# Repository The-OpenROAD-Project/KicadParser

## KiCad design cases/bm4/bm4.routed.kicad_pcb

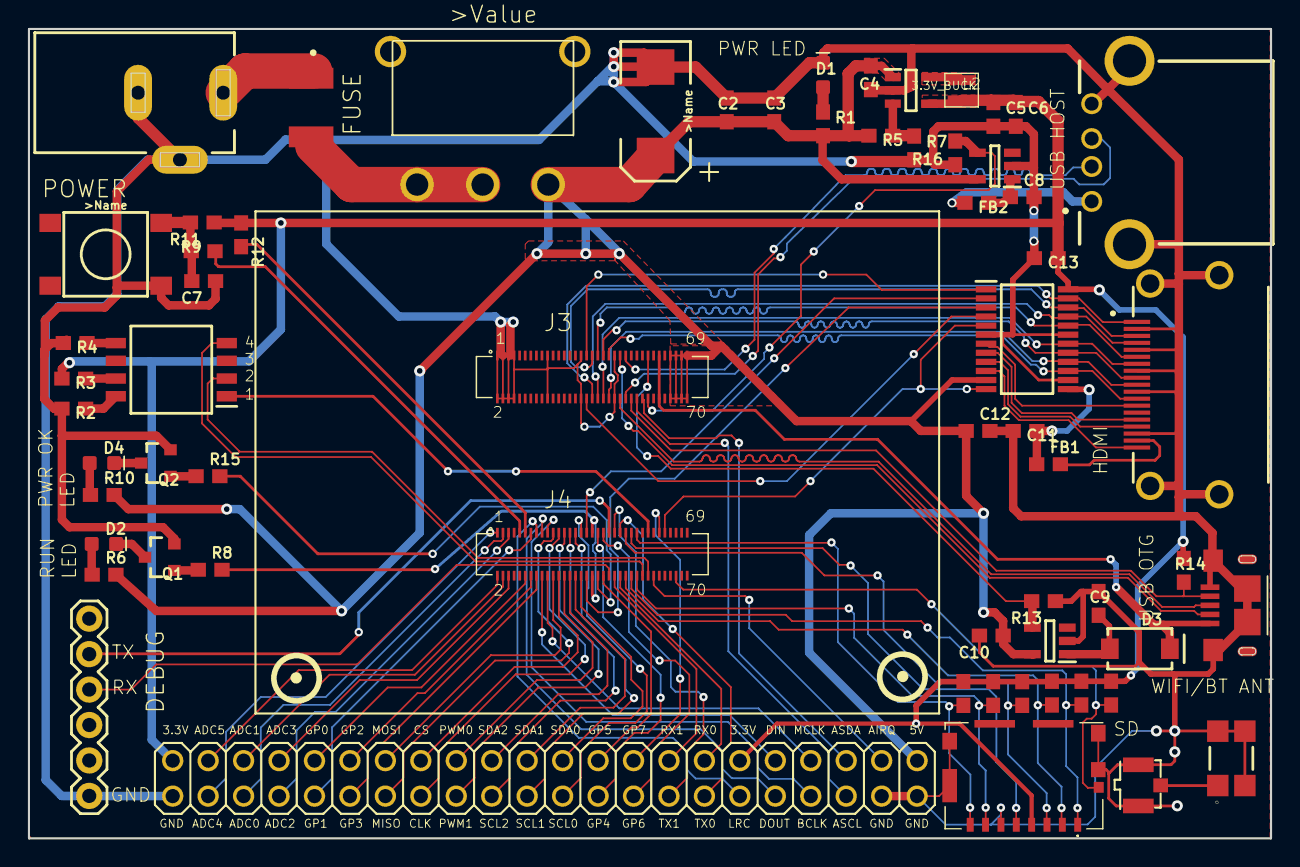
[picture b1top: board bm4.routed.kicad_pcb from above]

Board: 2 copper layers, 89.0 x 58.0 mm, 63 parts (0 on the bottom side), 103 nets.

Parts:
3.3V_BUCK: LM3671MF-3.3_NOPB; SOT95P284X122-5N
ANT1: 146175-0001
C1: 100uF; EIA7343
C2, C5, C10: 10uF; 0603
C3, C6, C11, C12, C13: 0.1uF; 0603
C4, C8, C9: 4.7uF; 0603
C7: 1.0uF; 0603
D1: Red; LED-0603
D2: GREEN; LED-0603
D3: 3A/40V/500mV; SMA-DIODE
D4: BLUE; LED-0603
F1: MF-MSMF260-2
FB1: 120Ω; 0603
FB2: 30Ω; 0603
IC2, IC4: TPS2051BDBVR; SOT95P280X145-5N
IC3: TPD12S016PWR; SOP65P640X120-24N
J1: DCJ0202
J2: 10118193-0001LF
J3, J4: DF40C(2.0)-70DS-0.4V(51)
J5: UE27AC54100
J6: 6_PIN_SERIAL_CABLEPTH; FTDI_BASIC
J7: 10029449-111RLF; 10029449-111RLF_1
J8: 1051620001
L2: NRH2412T2R2MNGH
Q1, Q2: 600mA/40V; SOT23-3
R1, R6, R10: 470; 0603
R2, R3, R4: 1k; 0603
R5, R8, R13, R15, R17, R20: 10k; 0603
R7, R11, R12, R14, R16: 100k; 0603
R9: 33; 0603
R18, R19, R21, R22: 51k; 0603
S1: MOMENTARY-SWITCH-SPST-SMD-6.2MM-TALL; TACTILE_SWITCH_SMD_6.2MM_TALL
S3: 218-4LPST; SOIC127P844X265-8N
SV1: TEST HEADER; 2X22
SW1: 500SSP1S1M6QEA
U$3: U.FL-R-SMT(10)

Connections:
3.3V: 3.3V_BUCK.4, C5.1, C6.1, C13.1, IC3.24, J8.4, L2.2, R3.2, R11.1, R12.1, R14.2, R17.2, R18.2, R19.2, R20.2, R21.2, R22.2, SV1.2, SV1.34
5V: 3.3V_BUCK.1, C1.A, C2.1, C3.1, C4.1, C10.1, C12.1, IC2.5, IC3.11, IC4.5, J3.63, J3.64, J3.65, J3.66, J3.67, J3.68, J3.69, J3.70, R1.2, R5.2, R6.2, R10.2, SV1.44, SW1.3
GND: 3.3V_BUCK.2, ANT1.2, ANT1.3, ANT1.4, C1.C, C2.2, C3.2, C4.2, C5.2, C6.2, C7.1, C8.2, C9.2, C10.2, C11.2, C12.2, C13.2, D1.C, IC2.2, IC3.6, IC3.14, IC3.19, IC4.2, J1.2, J1.3, J2.GND, J2.SHIELD$1, J2.SHIELD$2, J2.SHIELD$3, J2.SHIELD$4, J3.1, J3.2, J3.3, J3.4, J3.5, J3.6, J3.7, J3.8, J3.19, J3.20, J3.31, J3.32, J3.43, J3.44, J5.4, J5.5, J5.6, J6.GND, J7.2, J7.5, J7.8, J7.11, J7.17, J7.20, J7.21, J7.22, J7.23, J8.6, J8.10, J8.11, J8.12, J8.13, Q1.2, Q2.2, R2.2, R4.2, R7.2, R13.1, R16.1, S1.A2, SV1.1, SV1.41, SV1.43, U$3.1, U$3.2
unnamed: F1.1, J1.1
unnamed: F1.2, SW1.1, SW1.2
unnamed: 3.3V_BUCK.5, L2.1
unnamed: D1.A, R1.1
unnamed: R2.1, S3.8
unnamed: R3.1, S3.7
unnamed: R4.1, S3.5
unnamed: D2.A, R6.1
unnamed: 3.3V_BUCK.3, R5.1, R7.1
unnamed: D2.C, Q1.3
unnamed: Q1.1, R8.1
unnamed: C7.2, R9.1, R11.2, S1.B2
unnamed: D4.A, R10.1
unnamed: C11.1, FB1.1, IC3.13
unnamed: C9.1, D3.A, IC2.1
unnamed: IC3.7, J7.13
unnamed: IC3.8, J7.15
unnamed: IC3.9, J7.16
unnamed: IC3.10, J7.19
unnamed: D4.C, Q2.3
unnamed: Q2.1, R15.1
unnamed: FB1.2, J7.18
unnamed: C8.1, FB2.1, IC4.1
unnamed: FB2.2, J5.1
unnamed: ANT1.1, U$3.3
VCC5P0_OTG: D3.C, J2.VCC, J3.59, J3.60
VSYS_IO_3P3: J4.35, J4.36, R8.2
XADC0: J4.3, SV1.5
XADC1: J4.4, SV1.6
XADC2: J4.5, SV1.7
XADC3: J4.6, SV1.8
XADC4: J4.1, SV1.3
XADC5: J4.2, SV1.4
XAUDIO_IRQ: J4.58, SV1.42
XAUDIO_SCL: J3.52, SV1.39
XAUDIO_SDA: J3.54, SV1.40
XBOOT_CONFIG0: J4.55, S3.1
XBOOT_CONFIG1: J4.56, S3.2
XBOOT_CONFIG3: J4.54, S3.4
XDEBUG_RX: J4.42, J6.TXO
XDEBUG_TX: J4.41, J6.RXI
XGPA15: IC2.4, J3.55, R13.2
XGPA16: IC4.4, J3.56, R16.2
XGPA21: IC3.5, IC3.12, J4.61
XGPIO0: J4.12, SV1.10
XGPIO1: J4.13, SV1.9
XGPIO2: J4.14, SV1.12
XGPIO3: J4.16, SV1.11
XGPIO4: J4.37, SV1.25
XGPIO5: J4.40, SV1.26
XGPIO6: J4.39, SV1.27
XGPIO7: J4.59, SV1.28
XHDMI_CEC: IC3.1, J3.33
XHDMI_HPD: IC3.4, J3.34
XHDMI_I2C_SCL: IC3.2, J4.33
XHDMI_I2C_SDA: IC3.3, J4.34
XHDMI_TX0_N: IC3.17, J3.39, J7.9
XHDMI_TX0_P: IC3.18, J3.40, J7.7
XHDMI_TX1_N: IC3.20, J3.37, J7.6
XHDMI_TX1_P: IC3.21, J3.38, J7.4
XHDMI_TX2_N: IC3.22, J3.35, J7.3
XHDMI_TX2_P: IC3.23, J3.36, J7.1
XHDMI_TXC_N: IC3.15, J3.41, J7.12
XHDMI_TXC_P: IC3.16, J3.42, J7.10
XI2C_SCL0: J4.31, SV1.23
XI2C_SCL1: J4.29, SV1.21
XI2C_SCL2: J4.27, SV1.19
XI2C_SDA0: J4.32, SV1.24
XI2C_SDA1: J4.30, SV1.22
XI2C_SDA2: J4.28, SV1.20
XI2S0_BCLK: J4.19, SV1.37
XI2S0_DIN: J4.18, SV1.36
XI2S0_DOUT: J4.17, SV1.35
XI2S0_LRCLK: J4.15, SV1.33
XI2S0_MCLK: J4.20, SV1.38
XNRESET: J4.11, R12.2
XOTG_D_N: J2.D-, J3.45
XOTG_D_P: J2.D+, J3.46
XOTG_ID: J2.ID, J3.50, R14.1
XPWERKEY: J4.9, R9.2
XPWM0: J4.26, SV1.18
XPWM1: J4.25, SV1.17
XSD0_CDN: J4.66, J8.9, R17.1
XSD0_CLK: J4.49, J8.5
XSD0_CMD: J4.47, J8.3, R19.1
XSD0_D0: J4.52, J8.7, R20.1
XSD0_D1: J4.51, J8.8, R18.1
XSD0_D2: J4.50, J8.1, R21.1
XSD0_D3: J4.48, J8.2, R22.1
XSPI_CLK: J4.23, SV1.15
XSPI_CS: J4.24, SV1.16
XSPI_MISO: J4.21, SV1.13
XSPI_MOSI: J4.22, SV1.14
XUART_RX0: J4.46, SV1.32
XUART_RX1: J4.44, SV1.30
XUART_TX0: J4.45, SV1.31
XUART_TX1: J4.43, SV1.29
XUSBH_D_N: J3.47, J5.2
XUSBH_D_P: J3.48, J5.3
XVDDPWRON: J4.38, R15.2

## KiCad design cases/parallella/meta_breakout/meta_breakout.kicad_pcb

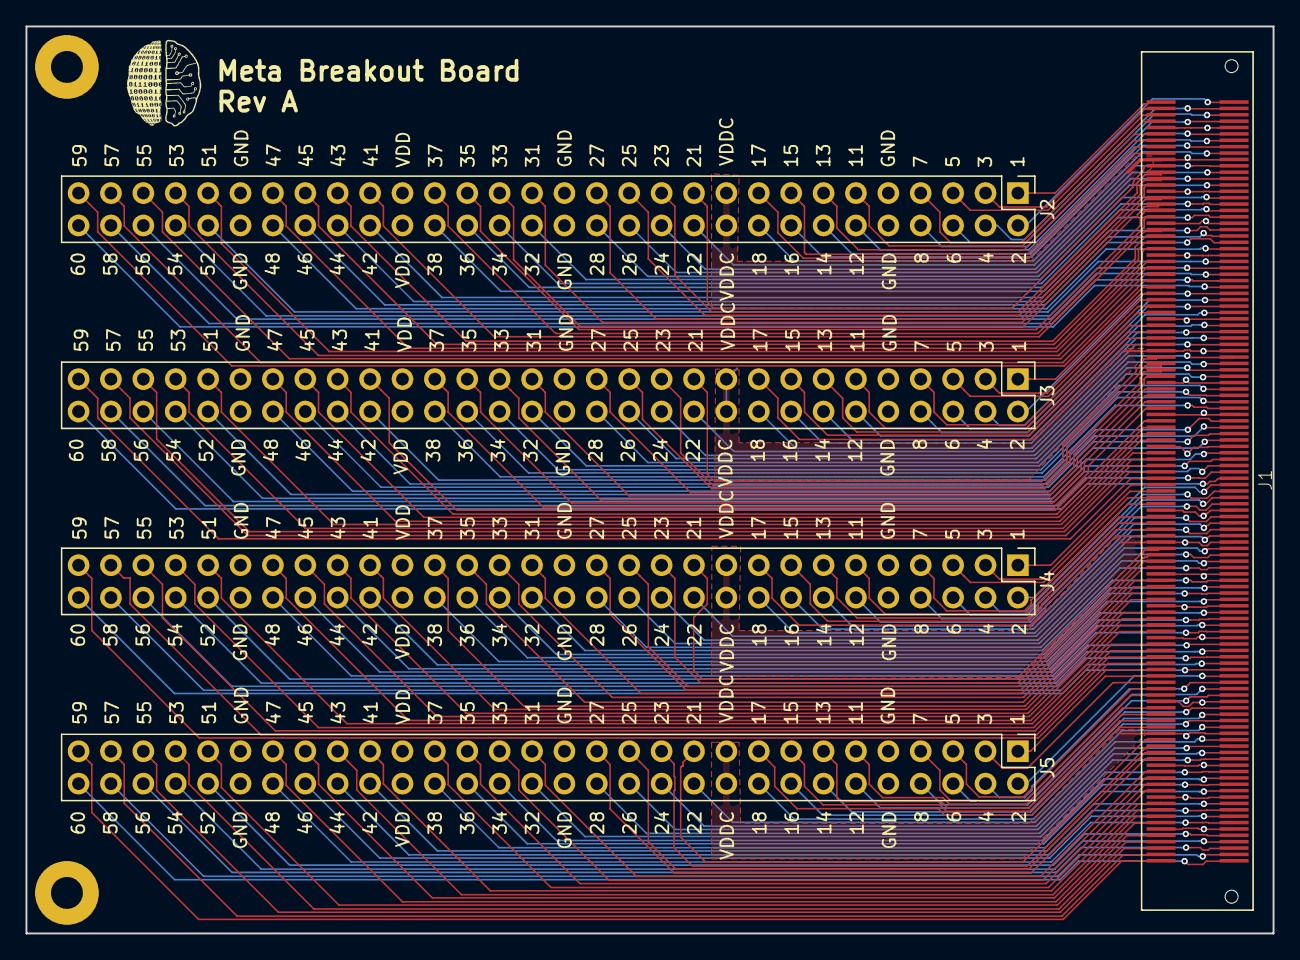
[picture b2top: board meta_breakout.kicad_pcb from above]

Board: 4 copper layers, 97.8 x 71.1 mm, 5 parts (0 on the bottom side), 209 nets.

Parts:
J1: BSH-120; BSH-120-01-X-D-A
J2, J3, J4, J5: Conn_02x30_Odd_Even; PinHeader_2x30_P2.54mm_Vertical

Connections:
/CTRL_IN0: J1.59, J2.59
/CTRL_IN1: J1.119, J3.59
/CTRL_IN2: J1.179, J4.59
/CTRL_IN3: J1.239, J5.59
/CTRL_OUT0: J1.60, J2.60
/CTRL_OUT1: J1.120, J3.60
/CTRL_OUT2: J1.180, J4.60
/CTRL_OUT3: J1.240, J5.60
/DATA_IN_N0: J1.21, J2.21
/DATA_IN_N1: J1.25, J2.25
/DATA_IN_N2: J1.31, J2.31
/DATA_IN_N3: J1.35, J2.35
/DATA_IN_N4: J1.41, J2.41
/DATA_IN_N5: J1.45, J2.45
/DATA_IN_N6: J1.51, J2.51
/DATA_IN_N7: J1.55, J2.55
/DATA_IN_N8: J1.81, J3.21
/DATA_IN_N9: J1.85, J3.25
/DATA_IN_N10: J1.91, J3.31
/DATA_IN_N11: J1.95, J3.35
/DATA_IN_N12: J1.101, J3.41
/DATA_IN_N13: J1.105, J3.45
/DATA_IN_N14: J1.111, J3.51
/DATA_IN_N15: J1.115, J3.55
/DATA_IN_N16: J1.141, J4.21
/DATA_IN_N17: J1.145, J4.25
/DATA_IN_N18: J1.151, J4.31
/DATA_IN_N19: J1.155, J4.35
/DATA_IN_N20: J1.161, J4.41
/DATA_IN_N21: J1.165, J4.45
/DATA_IN_N22: J1.171, J4.51
/DATA_IN_N23: J1.175, J4.55
/DATA_IN_N24: J1.201, J5.21
/DATA_IN_N25: J1.205, J5.25
/DATA_IN_N26: J1.211, J5.31
/DATA_IN_N27: J1.215, J5.35
/DATA_IN_N28: J1.221, J5.41
/DATA_IN_N29: J1.225, J5.45
/DATA_IN_N30: J1.231, J5.51
/DATA_IN_N31: J1.235, J5.55
/DATA_IN_P0: J1.23, J2.23
/DATA_IN_P1: J1.27, J2.27
/DATA_IN_P2: J1.33, J2.33
/DATA_IN_P3: J1.37, J2.37
/DATA_IN_P4: J1.43, J2.43
/DATA_IN_P5: J1.47, J2.47
/DATA_IN_P6: J1.53, J2.53
/DATA_IN_P7: J1.57, J2.57
/DATA_IN_P8: J1.83, J3.23
/DATA_IN_P9: J1.87, J3.27
/DATA_IN_P10: J1.93, J3.33
/DATA_IN_P11: J1.97, J3.37
/DATA_IN_P12: J1.103, J3.43
/DATA_IN_P13: J1.107, J3.47
/DATA_IN_P14: J1.113, J3.53
/DATA_IN_P15: J1.117, J3.57
/DATA_IN_P16: J1.143, J4.23
/DATA_IN_P17: J1.147, J4.27
/DATA_IN_P18: J1.153, J4.33
/DATA_IN_P19: J1.157, J4.37
/DATA_IN_P20: J1.163, J4.43
/DATA_IN_P21: J1.167, J4.47
/DATA_IN_P22: J1.173, J4.53
/DATA_IN_P23: J1.177, J4.57
/DATA_IN_P24: J1.203, J5.23
/DATA_IN_P25: J1.207, J5.27
/DATA_IN_P26: J1.213, J5.33
/DATA_IN_P27: J1.217, J5.37
/DATA_IN_P28: J1.223, J5.43
/DATA_IN_P29: J1.227, J5.47
/DATA_IN_P30: J1.233, J5.53
/DATA_IN_P31: J1.237, J5.57
/DATA_OUT_N0: J1.22, J2.22
/DATA_OUT_N1: J1.26, J2.26
/DATA_OUT_N2: J1.32, J2.32
/DATA_OUT_N3: J1.36, J2.36
/DATA_OUT_N4: J1.42, J2.42
/DATA_OUT_N5: J1.46, J2.46
/DATA_OUT_N6: J1.52, J2.52
/DATA_OUT_N7: J1.56, J2.56
/DATA_OUT_N8: J1.82, J3.22
/DATA_OUT_N9: J1.86, J3.26
/DATA_OUT_N10: J1.92, J3.32
/DATA_OUT_N11: J1.96, J3.36
/DATA_OUT_N12: J1.102, J3.42
/DATA_OUT_N13: J1.106, J3.46
/DATA_OUT_N14: J1.112, J3.52
/DATA_OUT_N15: J1.116, J3.56
/DATA_OUT_N16: J1.142, J4.22
/DATA_OUT_N17: J1.146, J4.26
/DATA_OUT_N18: J1.152, J4.32
/DATA_OUT_N19: J1.156, J4.36
/DATA_OUT_N20: J1.162, J4.42
/DATA_OUT_N21: J1.166, J4.46
/DATA_OUT_N22: J1.172, J4.52
/DATA_OUT_N23: J1.176, J4.56
/DATA_OUT_N24: J1.202, J5.22
/DATA_OUT_N25: J1.206, J5.26
/DATA_OUT_N26: J1.212, J5.32
/DATA_OUT_N27: J1.216, J5.36
/DATA_OUT_N28: J1.222, J5.42
/DATA_OUT_N29: J1.226, J5.46
/DATA_OUT_N30: J1.232, J5.52
/DATA_OUT_N31: J1.236, J5.56
/DATA_OUT_P0: J1.24, J2.24
/DATA_OUT_P1: J1.28, J2.28
/DATA_OUT_P2: J1.34, J2.34
/DATA_OUT_P3: J1.38, J2.38
/DATA_OUT_P4: J1.44, J2.44
/DATA_OUT_P5: J1.48, J2.48
/DATA_OUT_P6: J1.54, J2.54
/DATA_OUT_P7: J1.58, J2.58
/DATA_OUT_P8: J1.84, J3.24
/DATA_OUT_P9: J1.88, J3.28
/DATA_OUT_P10: J1.94, J3.34
/DATA_OUT_P11: J1.98, J3.38
/DATA_OUT_P12: J1.104, J3.44
/DATA_OUT_P13: J1.108, J3.48
/DATA_OUT_P14: J1.114, J3.54
/DATA_OUT_P15: J1.118, J3.58
/DATA_OUT_P16: J1.144, J4.24
/DATA_OUT_P17: J1.148, J4.28
/DATA_OUT_P18: J1.154, J4.34
/DATA_OUT_P19: J1.158, J4.38
/DATA_OUT_P20: J1.164, J4.44
/DATA_OUT_P21: J1.168, J4.48
/DATA_OUT_P22: J1.174, J4.54
/DATA_OUT_P23: J1.178, J4.58
/DATA_OUT_P24: J1.204, J5.24
/DATA_OUT_P25: J1.208, J5.28
/DATA_OUT_P26: J1.214, J5.34
/DATA_OUT_P27: J1.218, J5.38
/DATA_OUT_P28: J1.224, J5.44
/DATA_OUT_P29: J1.228, J5.48
/DATA_OUT_P30: J1.234, J5.54
/DATA_OUT_P31: J1.238, J5.58
/FRAME_IN_N0: J1.5, J2.5
/FRAME_IN_N1: J1.65, J3.5
/FRAME_IN_N2: J1.125, J4.5
/FRAME_IN_N3: J1.185, J5.5
/FRAME_IN_P0: J1.7, J2.7
/FRAME_IN_P1: J1.67, J3.7
/FRAME_IN_P2: J1.127, J4.7
/FRAME_IN_P3: J1.187, J5.7
/FRAME_OUT_N0: J1.6, J2.6
/FRAME_OUT_N1: J1.66, J3.6
/FRAME_OUT_N2: J1.126, J4.6
/FRAME_OUT_N3: J1.186, J5.6
/FRAME_OUT_P0: J1.8, J2.8
/FRAME_OUT_P1: J1.68, J3.8
/FRAME_OUT_P2: J1.128, J4.8
/FRAME_OUT_P3: J1.188, J5.8
/GND: J1.9, J1.10, J1.29, J1.30, J1.49, J1.50, J1.69, J1.70, J1.89, J1.90, J1.109, J1.110, J1.129, J1.130, J1.149, J1.150, J1.169, J1.170, J1.189, J1.190, J1.209, J1.210, J1.229, J1.230, J2.9, J2.10, J2.29, J2.30, J2.49, J2.50, J3.9, J3.10, J3.29, J3.30, J3.49, J3.50, J4.9, J4.10, J4.29, J4.30, J4.49, J4.50, J5.9, J5.10, J5.29, J5.30, J5.49, J5.50
/LCLK_IN_N0: J1.1, J2.1
/LCLK_IN_N1: J1.61, J3.1
/LCLK_IN_N2: J1.121, J4.1
/LCLK_IN_N3: J1.181, J5.1
/LCLK_IN_P0: J1.3, J2.3
/LCLK_IN_P1: J1.63, J3.3
/LCLK_IN_P2: J1.123, J4.3
/LCLK_IN_P3: J1.183, J5.3
/LCLK_OUT_N0: J1.2, J2.2
/LCLK_OUT_N1: J1.62, J3.2
/LCLK_OUT_N2: J1.122, J4.2
/LCLK_OUT_N3: J1.182, J5.2
/LCLK_OUT_P0: J1.4, J2.4
/LCLK_OUT_P1: J1.64, J3.4
/LCLK_OUT_P2: J1.124, J4.4
/LCLK_OUT_P3: J1.184, J5.4
/VDD0: J1.19, J1.20, J2.19, J2.20
/VDD1: J1.79, J1.80, J3.19, J3.20
/VDD2: J1.139, J1.140, J4.19, J4.20
/VDD3: J1.199, J1.200, J5.19, J5.20
/VDDIO0: J1.39, J1.40, J2.39, J2.40
/VDDIO1: J1.99, J1.100, J3.39, J3.40
/VDDIO2: J1.159, J1.160, J4.39, J4.40
/VDDIO3: J1.219, J1.220, J5.39, J5.40
/WAIT_RD_IN_N0: J1.16, J2.16
/WAIT_RD_IN_N1: J1.76, J3.16
/WAIT_RD_IN_N2: J1.136, J4.16
/WAIT_RD_IN_N3: J1.196, J5.16
/WAIT_RD_IN_P0: J1.18, J2.18
/WAIT_RD_IN_P1: J1.78, J3.18
/WAIT_RD_IN_P2: J1.138, J4.18
/WAIT_RD_IN_P3: J1.198, J5.18
/WAIT_RD_OUT_N0: J1.15, J2.15
/WAIT_RD_OUT_N1: J1.75, J3.15
/WAIT_RD_OUT_N2: J1.135, J4.15
/WAIT_RD_OUT_N3: J1.195, J5.15
/WAIT_RD_OUT_P0: J1.17, J2.17
/WAIT_RD_OUT_P1: J1.77, J3.17
/WAIT_RD_OUT_P2: J1.137, J4.17
/WAIT_RD_OUT_P3: J1.197, J5.17
/WAIT_WR_IN_N0: J1.12, J2.12
/WAIT_WR_IN_N1: J1.72, J3.12
/WAIT_WR_IN_N2: J1.132, J4.12
/WAIT_WR_IN_N3: J1.192, J5.12
/WAIT_WR_IN_P0: J1.14, J2.14
/WAIT_WR_IN_P1: J1.74, J3.14
/WAIT_WR_IN_P2: J1.134, J4.14
/WAIT_WR_IN_P3: J1.194, J5.14
/WAIT_WR_OUT_N0: J1.11, J2.11
/WAIT_WR_OUT_N1: J1.71, J3.11
/WAIT_WR_OUT_N2: J1.131, J4.11
/WAIT_WR_OUT_N3: J1.191, J5.11
/WAIT_WR_OUT_P0: J1.13, J2.13
/WAIT_WR_OUT_P1: J1.73, J3.13
/WAIT_WR_OUT_P2: J1.133, J4.13
/WAIT_WR_OUT_P3: J1.193, J5.13

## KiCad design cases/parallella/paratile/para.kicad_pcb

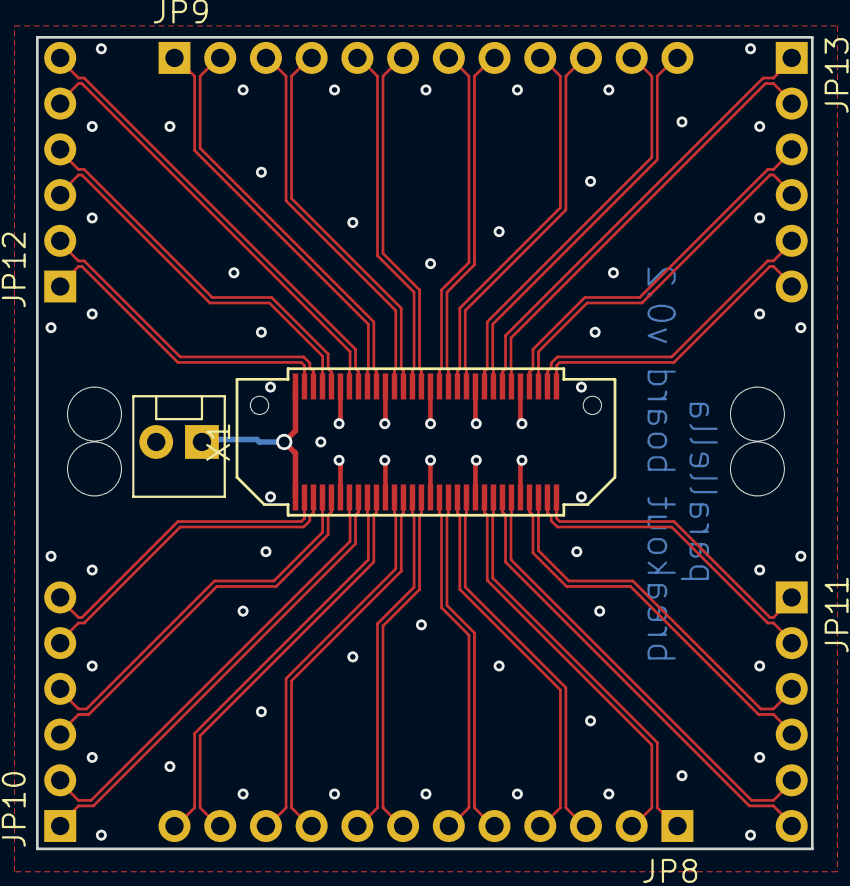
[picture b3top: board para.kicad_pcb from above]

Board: 2 copper layers, 43.1 x 45.1 mm, 13 parts (0 on the bottom side), 50 nets.

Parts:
@HOLE0, @HOLE1, @HOLE2, @HOLE3: (no value)
C2: CAP0805; 0805
JP7: M02POLAR; MOLEX-1X2
JP8, JP9: PINHD-1X12-CB; 1X12-CB
JP10, JP11, JP12, JP13: PINHD-1X6CB; 1X06-CLEANBIG
X1: BTH-030-XX-X-D-A

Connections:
GND: C2.2, JP7.2, X1.11, X1.12, X1.21, X1.22, X1.31, X1.32, X1.41, X1.42, X1.51, X1.52
unnamed: JP8.1, X1.46
unnamed: JP8.2, X1.44
unnamed: JP8.3, X1.40
unnamed: JP8.4, X1.38
unnamed: JP8.5, X1.36
unnamed: JP8.6, X1.34
unnamed: JP8.7, X1.30
unnamed: JP8.8, X1.28
unnamed: JP8.9, X1.26
unnamed: JP8.10, X1.24
unnamed: JP8.11, X1.20
unnamed: JP8.12, X1.18
unnamed: JP9.1, X1.17
unnamed: JP9.2, X1.19
unnamed: JP9.3, X1.23
unnamed: JP9.4, X1.25
unnamed: JP9.5, X1.27
unnamed: JP9.6, X1.29
unnamed: JP9.7, X1.33
unnamed: JP9.8, X1.35
unnamed: JP9.9, X1.37
unnamed: JP9.10, X1.39
unnamed: JP9.11, X1.43
unnamed: JP9.12, X1.45
unnamed: JP10.1, X1.16
unnamed: JP10.2, X1.14
unnamed: JP10.3, X1.10
unnamed: JP10.4, X1.8
unnamed: JP10.5, X1.6
unnamed: JP10.6, X1.4
unnamed: JP11.1, X1.60
unnamed: JP11.2, X1.58
unnamed: JP11.3, X1.56
unnamed: JP11.4, X1.54
unnamed: JP11.5, X1.50
unnamed: JP11.6, X1.48
unnamed: JP12.1, X1.3
unnamed: JP12.2, X1.5
unnamed: JP12.3, X1.7
unnamed: JP12.4, X1.9
unnamed: JP12.5, X1.13
unnamed: JP12.6, X1.15
unnamed: JP13.1, X1.47
unnamed: JP13.2, X1.49
unnamed: JP13.3, X1.53
unnamed: JP13.4, X1.55
unnamed: JP13.5, X1.57
unnamed: JP13.6, X1.59
VCC: C2.1, JP7.1, X1.1, X1.2
